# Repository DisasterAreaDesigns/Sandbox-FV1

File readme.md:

# FV-1 Sandbox
FV-1 Sandbox is a self-contained open-source development platform for the Spin FV-1 digital signal processing (DSP) integrated circuit.  

## Background:
The Spin Semiconductor FV-1 IC was developed by Alesis alumni Keith Barr and Frank Thomson.  It features an integrated architecture with built-in analog-to-digital and digital-to-analog converters, memory, and processing core.  It requires only a few external components to operate, and can run user programs from an inexpensive serial EEPROM.  It has been used in hundreds of different pedals and devices, with many hundreds of thousands of units in service.

## Why Are We Doing This?
The FV-1 has seven built-in programs that cover a wide range of effects, but most designers leverage the custom code capabilities of the chip.  The Fv-1 is programmed in SpinASM, a proprietary assembly language.  Spin provided a free integrated development environment for Windows computers called SpinASM IDE.  This interfaces with a development board fitted with a Cypress PSoC microcontroller functioning as a USB interface.  The IDE allows for code editing, rapid auditioning of DSP algorithms on the development board, and production programming using multi-algorithm .SPJ Spin Project files.  No MacOS or Linux programming tools were made available, and SpinASM also had issues running on newer versions of Windows.  A patch was released to fix compatibility issues under Windows 7, and this version (1.1.31) works with most Windows 10 and Windows 11 systems.  The IDE does also run under Windows for ARM, but support for the PSoC-based development board is broken due to driver issues.

Our intention is to create a complete toolchain that can run on any modern computer that interfaces with a high-quality hardware platform for deploying algorithms.  To this end, we have created an open-source assembler that runs in a web browser and a hardware platform that interfaces with an inexpensive RP2040 microcontroller for programming.  The hardware platform may be assembled without the microcontroller for higher-quantity production use, and the RP2040 programmer may be used in conjunction with either a TagConnect programming cable or pin sockets on the PCB for production programming.

## What Did We Do?
We've been using [asfv1](https://github.com/ndf-zz/asfv1), an open-source assembler for FV-1 designed by Nathan Fraser.  It works great but requires a few steps to deploy as part of a larger toolchain.  It works with Sublime Text or Notepad++ to create a DIY development environment, but it's still a lot of work for a new user.  So we decided to build a one-stop shop!

We patched up some bugs we found, added some quality-of-life improvements, and ported the whole thing from Python to JavaScript so we could run it in a browser.  There's a pretty decent code editor using Monaco, an assembler, and a one-button deployment to the Sandbox hardware.

The hardware is very simple, incorporating a high-quality analog front-end that reduces out-of-band and clock noise from the FV-1.  It's full stereo, features three user potentiometer controls, and two toggle switches for selecting one of six possible algorithms.  It also uses program zero to bypass the effect, allowing stereo switching without any external hardware or relays, albeit at the cost of higher noise floor and a slight delay from the DSP ADC+DAC conversions.

Programming is accomplished using the aforementioned RP2040 board - we've used a Waveshare RP2040 Zero for its compact form factor and handy USB-C port, but clones of this part or other variations may also work.  the RP2040 code is implemented in CircuitPython for ease of deployment and modification.  To program a new algorithm on the Sandbox EEPROM, simply copy an assembled .HEX or .BIN file to the RP2040 CIRCUITPY or SANDBOX removable drive.  Name the program 0.HEX to program algorithm zero, 1.HEX for program 1, and so on.  Adding any other named .BIN or .HEX file will write program #3, which is the program accessed if no toggle switches are assembled to the Sandbox PCBA.

We've also added an FV-1 simulator to the web app.  The assembled program runs through a software model of the chip at its native 32.768 kHz, so you can audition an algorithm on a test tone, an audio file, or live input before you ever program the hardware.  The three pot controls are on screen, and each successful build reloads into the simulator while it plays.  Two indicator lamps follow `REG30` and `REG31`.  The simulator models accumulator saturation and the FV-1's companded delay memory, and its LFO rates and depths follow the equations in Spin's application note AN-0001.  Chorus interpolation is approximated, so always confirm a design on real hardware.

The simulator can also be played from a MIDI controller plugged into your computer.  Press **Enable MIDI** in the simulator panel, allow the browser's MIDI prompt, and pick an input and channel.  `CC50`, `CC51` and `CC52` sweep POT0, POT1 and POT2, and `CC102` switches the effect, with `0-63` bypassed and `64-127` engaged.  MIDI moves the same controls the sliders do, at the full 128 steps a control change carries, so a program cannot tell the difference between a fader and a mouse.  Note that the Sandbox pedal itself has no MIDI input - this drives the simulator only.

The simulator can be watched as well as heard.  **Open register viewer**, under **Debug Tools** in the simulator panel, opens a second window (floating above the editor where the browser allows it, with an **Always on top** switch in its header) showing `ACC`, the audio in and out, the pots, the LFOs and `REG0`-`REG31` as the program runs, each as its S.23 value and the 24-bit word behind it, and named after the `EQU` lines in your source.  Click a register there to plot it over time - an audio-rate signal shows as its envelope and an LFO as its shape.  **ACC trace in editor** writes the accumulator after every instruction at the end of its line, live: a `SKP` says whether it was taken, the lines it jumped over say so, and a line whose result had to be clamped shows how often that happens.  The FV-1 runs every instruction every sample, so one pass is a complete trace and there is nothing to step through to see it.

When there is, the **Debug** section halts the simulator and steps it.  **Halt** freezes the core at the end of the current sample; **Step** runs one instruction, **Sample** runs the rest of the pass, and **Run to line** goes on until that line is next, with the editor following, the trace showing this pass up to the halt, and the register viewer updating on every step.  Breakpoints are conditions rather than places, since a bare line would trip on the first sample: click the margin left of a line number for a line breakpoint and give it a first run or a sample number, or halt on a clip, a `SKP` going one way, or `ACC` or a register crossing a value.  While halted the output is silent and the input is held at the halted sample; **Resume** carries on from wherever the stepping got to.

So it's a web app and a pedal.  Hook 'em up and write some code!

## Running the Assembler Locally
The web app needs to be served over http - opening `Assembler/index.html` directly as a `file://` page will not work.  Browsers block the audio engine the simulator depends on from `file://` origins, and the directory and serial access used to talk to the hardware need a secure context too.  `localhost` counts as secure, so any static file server will do:

```
python3 -m http.server 8000 --directory Assembler
```

Then open <http://localhost:8000> in Chrome or Edge.  If you prefer Node, `npx serve Assembler` works the same way.

Chrome or Edge are required for programming hardware and selecting folders, since Firefox and Safari do not implement the File System Access and Web Serial APIs.  The simulator itself works in any browser with AudioWorklet support, and its MIDI control works in Chrome, Edge and Firefox - Safari has no Web MIDI.

## What's In This Repo?
* **ASFV1 Source:**  copies of the Python source for asfv1, the reference assembler this one is checked against
* **Assembler:**  JavaScript Web Application for assembling FV-1 programs, including an in-browser FV-1 simulator (`fv1-emu.js` / `fv1-sim.js`) with MIDI control (`fv1-midi.js`), a register viewer (`fv1-regs.js`), an ACC trace in the editor (`fv1-trace.js`) and a halt-and-step debugger with conditional breakpoints (`fv1-debug.js`)
* **Firmware**  CircuitPython code for the RP2040 Zero program module
* **spin-test**  Puppeteer scripts and sample FV-1 programs for testing the assembler: `npm run test:roundtrip` for the assembler and simulator as a pair, `npm run test:emu` for the DSP core, `npm run test:midi` for the simulator's MIDI control, and `npm run test:page` for the editor's unsaved-changes guard
* **Hardware**  Schematic and PCB files for Sandbox pedal hardware

## What Can I Do With All This?
We've released this project and all associated tools under the [MIT License.](https://www.tldrlegal.com/license/mit-license)  This means that you can use the tools and information in this repository for anything you want, as long as you inform your users / customers / clients that you got it from us.  You can modify or change anything here to suit your purposes, and you can make products that you sell for profit.  You can even close your sources, so that what's in your product or project is private.  You just have to credit us as shown in our [license file.](https://github.com/DisasterAreaDesigns/Sandbox-FV1/blob/main/LICENSE)  An example of what that looks like can be found in our [Third Party Notices](https://github.com/DisasterAreaDesigns/Sandbox-FV1/blob/main/ThirdPartyNotices.txt) file.

Any projects you create with these tools belong to you.  If you write your own code to process audio with this project, that code is under your copyright and is yours to do with what you wish.  If you use someone else's DSP algorithms, that use will be subject to *their* license terms, and we're not able to help you sort that out.  TL:DR you can do whatever you want with this repo, just give us credit.

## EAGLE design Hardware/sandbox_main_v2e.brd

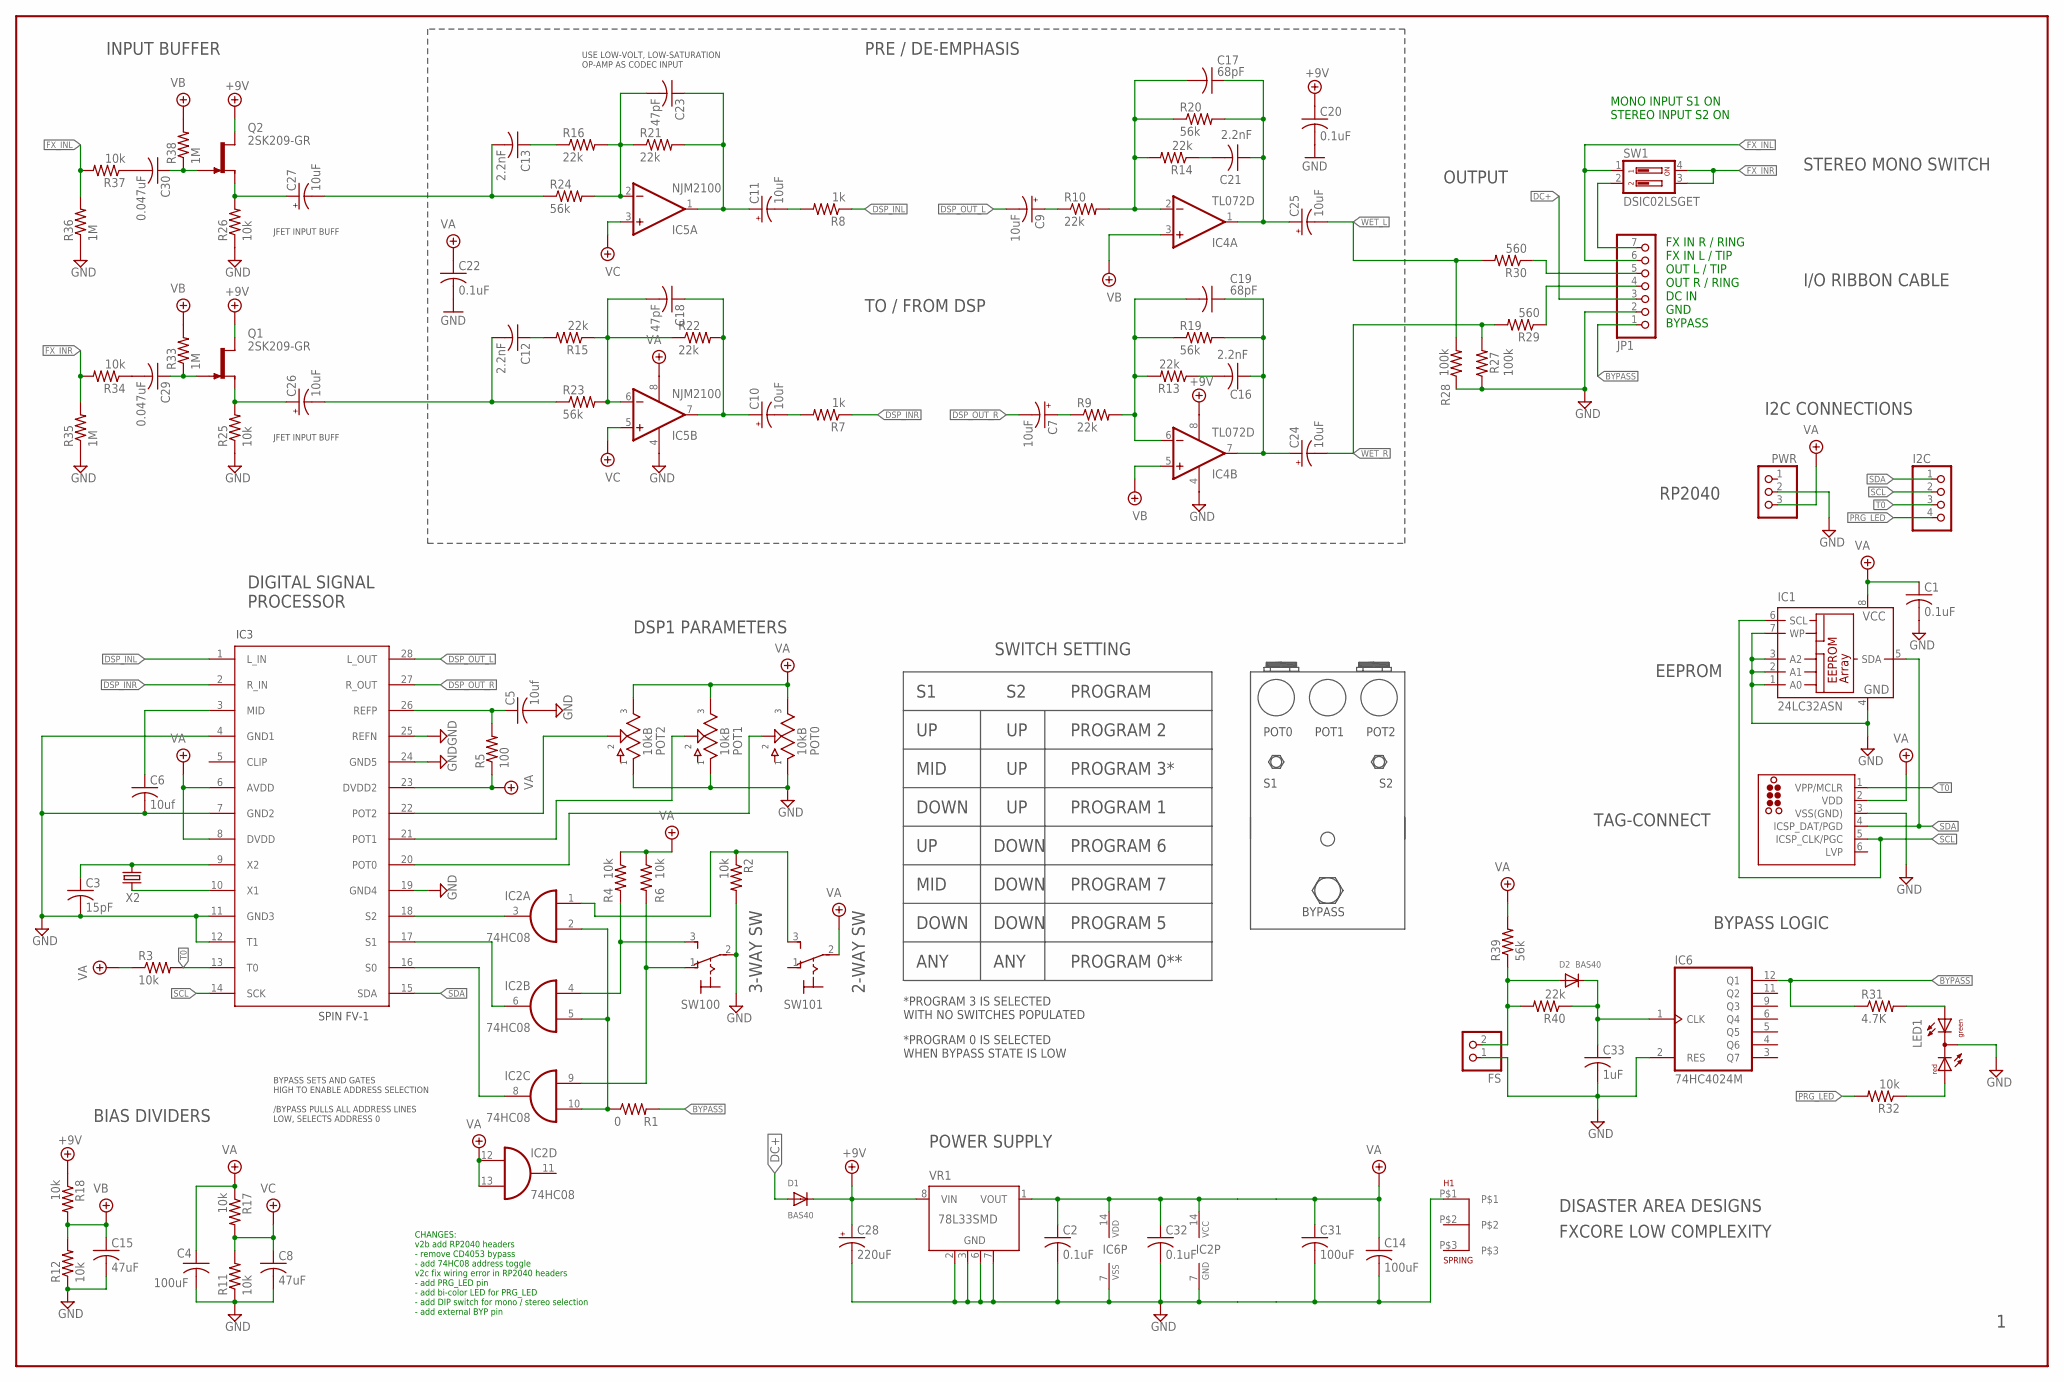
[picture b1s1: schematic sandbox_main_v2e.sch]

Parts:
C1, C2, C20, C22, C32: 0.1uF; C0805K
C3: 15pF; C0805K
C4, C14, C31: 100uF; C1206K
C5, C6: 10uf; C0805K
C7, C9, C10, C11, C24, C25, C26, C27: 10uF; CT3216
C8, C15: 47uF; C1206K
C12, C13, C16, C21: 2.2nF; C0805K
C17, C19: 68pF; C0805K
C18, C23: 47pF; C0805K
C28: 220uF; PANASONIC_D
C29, C30: 0.047uF; C1206K
C33: 1uF; C0805K
D1, D2: BAS40; SOT23-R
FS: PINHD-1X2; 1X02
H1: 628
I2C: PINHD-1X4; 1X04
IC1: 24LC32ASN; SO-08
IC2: 74HC08; SO14
IC3: SPINFV-1; SOIC-28
IC4: TL072D; SO08
IC5: NJM2100; SO08
IC6: 74HC4024M; SO14
JP1: PINHD-1X7; 1X07
LED1: DUOLED-RG-C; DUOLED-C-5MM
POT0, POT1, POT2: 10kB; POT_9MM_PACK_SM
PWR: PINHD-1X3; 1X03
Q1, Q2: 2SK209-GR; SOT-23
R1: 0; R0805
R2, R3, R4, R6, R11, R12, R17, R18, R25, R26, R32, R34, R37: 10k; R0805
R5: 100; R0805
R7, R8: 1k; R0805
R9, R10, R13, R14, R15, R16, R21, R22, R40: 22k; R0805
R19, R20, R23, R24, R39: 56k; R0805
R27, R28: 100k; R0805
R29, R30: 560; R0805
R31: 4.7K; R0805
R33, R35, R36, R38: 1M; R0805
SW1: DSIC02LSGET; CTS-219-02
SW100, SW101: 320-916
TC1: TC2030_ICSP-MCP-NL; TC2030-MCP-NL
VR1: 78L33SMD; SO08
X2: 32.768kHz; CRYSTAL-SMD-3.2X1.5MM

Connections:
+9V: C20.1, C28.+, D1.3 (C), IC4.8 (V+), Q1.2 (D), Q2.2 (D), R18.1, VR1.8 (VIN)
BYPASS: IC6.12 (Q1), JP1.1, R1.2, R31.1
BYPASS_IC: IC2.2 (I1), IC2.5 (I1), IC2.10 (I1), R1.1
DC+: D1.1 (A), JP1.3
DSP_INL: IC3.1 (L_IN), R8.1
DSP_INR: IC3.2 (R_IN), R7.1
DSP_OUT_L: C9.-, IC3.28 (L_OUT)
DSP_OUT_R: C7.-, IC3.27 (R_OUT)
FX_INL: JP1.6, R36.2, R37.2, SW1.1
FX_INR: R34.2, R35.2, SW1.3, SW1.4
GND: C1.2, C2.2, C3.2, C4.2, C5.2, C6.2, C8.2, C14.2, C15.2, C20.2, C22.2, C28.-, C31.2, C32.2, C33.2, FS.1, H1.P$1, IC1.1 (A0), IC1.2 (A1), IC1.3 (A2), IC1.4 (GND), IC1.7 (WP), IC2.7 (GND), IC3.4 (GND1), IC3.7 (GND2), IC3.11 (GND3), IC3.12 (T1), IC3.19 (GND4), IC3.24 (GND5), IC3.25 (REFN), IC4.4 (V-), IC5.4 (V-), IC6.2 (RES), IC6.7 (VSS), JP1.2, LED1.C, POT0.P$1, POT1.P$1, POT2.P$1, PWR.2, R2.2, R11.1, R12.1, R25.1, R26.1, R27.1, R28.1, R35.1, R36.1, SW100.2, TC1.3 (VSS(GND)), VR1.2 (GND), VR1.3 (GND), VR1.6 (GND), VR1.7 (GND)
unnamed: IC3.10 (X1), X2.P$1 (1)
unnamed: IC2.3 (O), IC3.18 (S2)
unnamed: C29.1, Q1.3 (G), R33.1
unnamed: IC2.6 (O), IC3.17 (S1)
unnamed: C29.2, R34.1
unnamed: IC2.8 (O), IC3.16 (S0)
unnamed: C11.+, C23.1, IC5.1 (OUT), R21.2
unnamed: C23.2, IC5.2 (-IN), R16.2, R21.1, R24.2
unnamed: C12.2, C26.-, R23.1
unnamed: C12.1, R15.2
unnamed: LED1.AR, R32.1
unnamed: JP1.7, SW1.2
unnamed: C13.1, R16.1
unnamed: C5.1, IC3.26 (REFP), R5.2
unnamed: C13.2, C27.-, R24.1
unnamed: C10.-, R7.2
unnamed: C6.1, IC3.3 (MID)
unnamed: C18.2, IC5.6 (-IN), R15.1, R22.1, R23.2
unnamed: C10.+, C18.1, IC5.7 (OUT), R22.2
unnamed: C17.2, IC4.2 (-IN), R10.2, R14.2, R20.1
unnamed: C11.-, R8.2
unnamed: C19.2, IC4.6 (-IN), R9.2, R13.2, R19.1
unnamed: C30.2, R37.1
unnamed: C7.+, R9.1
unnamed: C16.2, R13.1
unnamed: C16.1, C19.1, C24.+, IC4.7 (OUT), R19.2
unnamed: C9.+, R10.1
unnamed: JP1.5, R30.1
unnamed: C21.2, R14.1
unnamed: C17.1, C21.1, C25.+, IC4.1 (OUT), R20.2
unnamed: JP1.4, R29.1
unnamed: C33.1, D2.3 (C), IC6.1 (CLK), R40.1
unnamed: D2.1 (A), FS.2, R39.1, R40.2
unnamed: LED1.AX (AG), R31.2
unnamed: C3.1, IC3.9 (X2), X2.P$2 (2)
unnamed: C26.+, Q1.1 (S), R25.2
unnamed: C27.+, Q2.1 (S), R26.2
unnamed: C30.1, Q2.3 (G), R38.1
P0: IC3.20 (POT0), POT0.P$2
P1: IC3.21 (POT1), POT1.P$2
P2: IC3.22 (POT2), POT2.P$2
PRG_LED: I2C.4, R32.2
S0: IC2.9 (I0), R6.2, SW100.1 (O)
S1: IC2.4 (I0), R4.2, SW100.3 (S)
S2: IC2.1 (I0), R2.1, SW101.3 (S)
SCL: I2C.2, IC1.6 (SCL), IC3.14 (SCK), TC1.5 (ICSP_CLK/PGC)
SDA: I2C.1, IC1.5 (SDA), IC3.15 (SDA), TC1.4 (ICSP_DAT/PGD)
T0: I2C.3, IC3.13 (T0), R3.2, TC1.1 (VPP/MCLR)
VA: C1.1, C2.1, C4.1, C14.1, C22.1, C31.1, C32.1, IC1.8 (VCC), IC2.12 (I0), IC2.13 (I1), IC2.14 (VCC), IC3.6 (AVDD), IC3.8 (DVDD), IC3.23 (DVDD2), IC5.8 (V+), IC6.14 (VDD), POT0.P$3, POT1.P$3, POT2.P$3, PWR.3, R3.1, R4.1, R5.1, R6.1, R17.1, R39.2, SW101.2, TC1.2 (VDD), VR1.1 (VOUT)
VB: C15.1, IC4.3 (+IN), IC4.5 (+IN), R12.2, R18.2, R33.2, R38.2
VC: C8.1, IC5.3 (+IN), IC5.5 (+IN), R11.2, R17.2
WET_L: C25.-, R28.2, R30.2
WET_R: C24.-, R27.2, R29.2

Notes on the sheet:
POWER SUPPLY
DIGITAL SIGNAL PROCESSOR
INPUT BUFFER
FXCORE LOW COMPLEXITY
DSP1 PARAMETERS
3-WAY SW
DISASTER AREA DESIGNS
OUTPUT
POT2
POT1
POT0
BYPASS
BIAS DIVIDERS
SWITCH SETTING
MID
DOWN
PROGRAM 3*
PROGRAM 2
PROGRAM 1
PRE / DE-EMPHASIS
BYPASS LOGIC
USE LOW-VOLT, LOW-SATURATION OP-AMP AS CODEC INPUT
JFET INPUT BUFF
FX IN R / RING FX IN L / TIP OUT L / TIP OUT R / RING DC IN GND BYPASS
PROGRAM 7
PROGRAM 6
PROGRAM 5
PROGRAM
*PROGRAM 3 IS SELECTED WITH NO SWITCHES POPULATED
2-WAY SW
I2C CONNECTIONS
BYPASS SETS AND GATES HIGH TO ENABLE ADDRESS SELECTION /BYPASS PULLS ALL ADDRESS LINES LOW, SELECTS ADDRESS 0
CHANGES: v2b add RP2040 headers - remove CD4053 bypass - add 74HC08 address toggle v2c fix wiring error in RP2040 headers - add PRG_LED pin - add bi-color LED for PRG_LED - add DIP switch for mono / stereo selection - add external BYP pin
ANY
PROGRAM 0**
*PROGRAM 0 IS SELECTED WHEN BYPASS STATE IS LOW
MONO INPUT S1 ON STEREO INPUT S2 ON
SPIN FV-1
IC3
I/O RIBBON CABLE

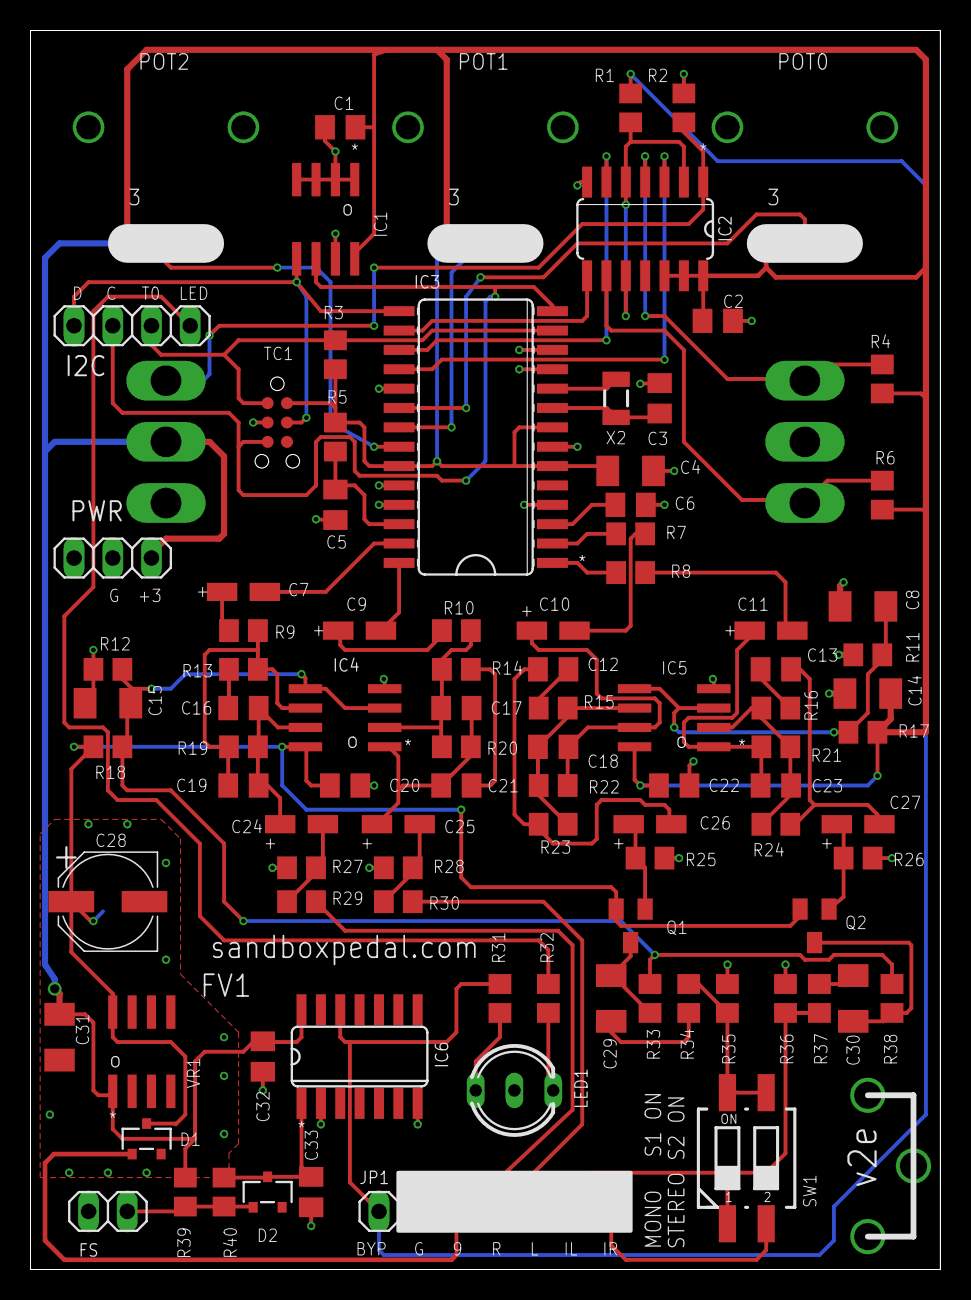
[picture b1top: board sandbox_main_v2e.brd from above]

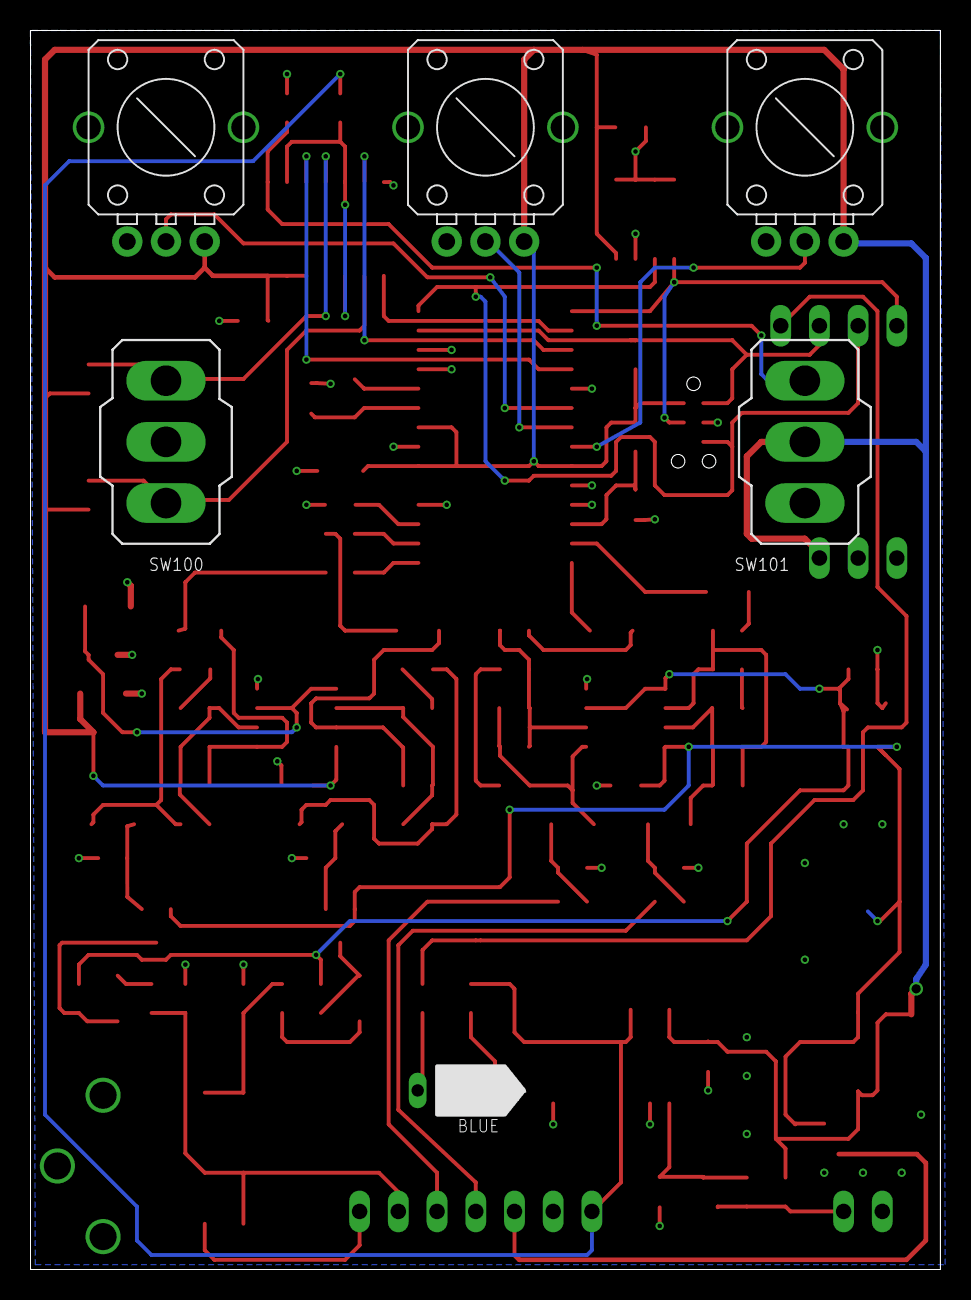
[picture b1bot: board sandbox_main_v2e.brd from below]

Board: 2 copper layers, 59.7 x 81.3 mm, 98 parts (2 on the bottom side), 64 nets.

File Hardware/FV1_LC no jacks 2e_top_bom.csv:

Comment,Designator,Footprint,LCSC Part #,Type
0,R1,R0805,,SMD
0.1uF,C1 C2 C20 C22 C32,C0805K,,SMD
0.047uF,C29 C30,C1206K,,SMD
1M,R33 R35 R36 R38,R0805,,SMD
1k,R7 R8,R0805,,SMD
1uF,C33,C0805K,,SMD
2.2nF,C12 C13 C16 C21,C0805K,,SMD
2SK209-GR,Q1 Q2,SOT-23,,SMD
4.7K,R31,R0805,,SMD
10k,R2 R3 R4 R6 R11 R12 R17 R18 R25 R26 R32 R34 R37,R0805,,SMD
10kB,POT0 POT1 POT2,POT_9MM_PACK_SM,,THT
10uF,C7 C9 C10 C11 C24 C25 C26 C27,CT3216,,SMD
10uf,C5 C6,C0805K,,SMD
15pF,C3,C0805K,,SMD
22k,R9 R10 R13 R14 R15 R16 R21 R22 R40,R0805,,SMD
24LC32ASN,IC1,SO-08,,SMD
32.768kHz,X2,CRYSTAL-SMD-3.2X1.5MM,,SMD
47pF,C18 C23,C0805K,,SMD
47uF,C8 C15,C1206K,,SMD
56k,R19 R20 R23 R24 R39,R0805,,SMD
68pF,C17 C19,C0805K,,SMD
74HC08,IC2,SO14,,SMD
74HC4024M,IC6,SO14,,SMD
78L33SMD,VR1,SO08,,SMD
100,R5,R0805,,SMD
100k,R27 R28,R0805,,SMD
100uF,C4 C14 C31,C1206K,,SMD
220uF,C28,PANASONIC_D,,SMD
560,R29 R30,R0805,,SMD
628,H1,628,,THT
BAS40,D1 D2,SOT23-R,,SMD
DSIC02LSGET,SW1,CTS-219-02,,SMD
NJM2100,IC5,SO08,,SMD
SPINFV-1,IC3,SOIC-28,,SMD
TL072D,IC4,SO08,,SMD

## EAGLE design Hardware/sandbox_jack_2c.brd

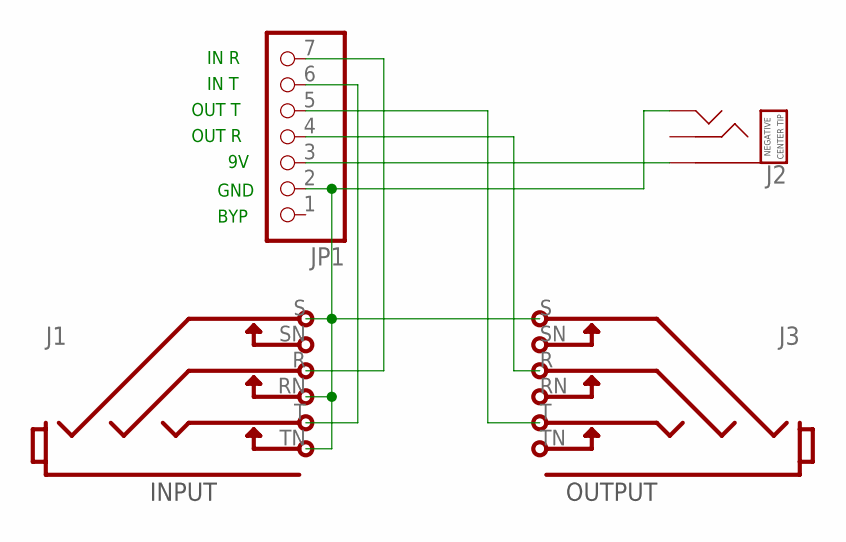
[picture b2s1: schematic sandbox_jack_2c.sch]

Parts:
J1, J3: STEREOSW3NOMOUNT; NEUTRIK-NRJ6HF-NOMOUNT
J2: DC_TRS; JACK_DC_PC-MOUNT_2.1MM_NO-KEEPOUT
JP1: PINHD-1X7; 1X07

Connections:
JACK_GND: J1.RN, J1.S, J1.TN, J2.3 (GND), J3.S, JP1.2
unnamed: J1.R, JP1.7
unnamed: J2.1 (PWR), JP1.3
unnamed: J1.T, JP1.6
unnamed: J3.T, JP1.5
unnamed: J3.R, JP1.4

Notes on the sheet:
INPUT
OUTPUT
GND
OUT T
IN T
OUT R
IN R
BYP

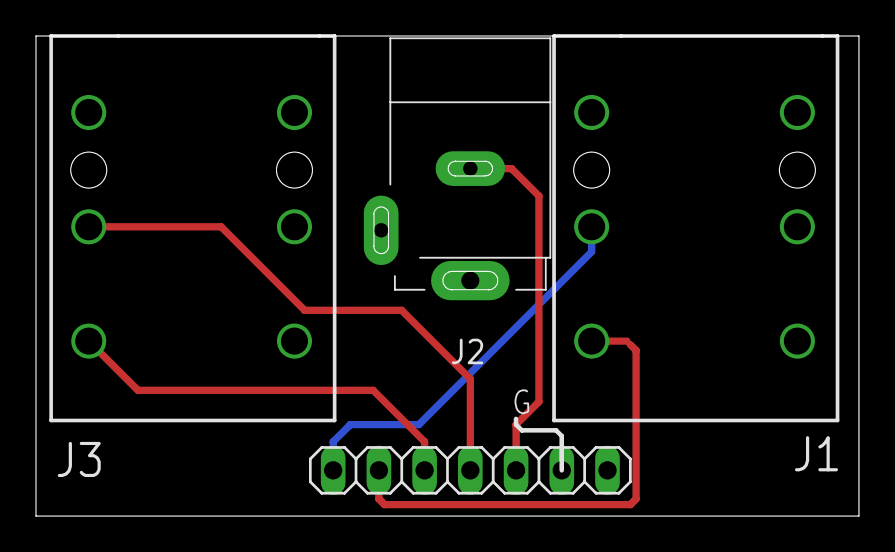
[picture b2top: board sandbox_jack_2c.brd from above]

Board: 2 copper layers, 45.7 x 26.7 mm, 4 parts (0 on the bottom side), 6 nets.

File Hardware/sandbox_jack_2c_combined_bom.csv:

Comment,Designator,Footprint,LCSC Part #,Type
,JP1,1X05,,THT
DC_TRS,J2,JACK_DC_PC-MOUNT_2.1MM_NO-KEEPOUT,,THT
STEREOSW3NOMOUNT,J1 J3,NEUTRIK-NRJ6HF-NOMOUNT,,THT

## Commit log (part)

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2025-08-01 Added readme.md
2025-08-01 Added readmes
2025-08-04 Initial commit
    Changed plaintext editor to use monaco instead
2025-08-04 Updated editor version
    Added icon, search / find text, title
2025-08-04 Fix issue with saving source
2025-08-04 Added favico
2025-08-04 Clean up, change examples to grid
2025-08-04 removed test file
2025-08-04 Update Program Selection grid
2025-08-04 Update readme.md
    Spelling and grammar
2025-08-05 Scroll window to top on load
2025-08-06 Update readme
    Added license terms and info
2025-08-06 Add .gitignore
2025-08-06 Build 10
    Split assembler and examples into their own files
    added modal popups to prevent accidental clearing
    added note to editor window re: ascii only
2025-08-06 Added proper dark mode
2025-08-06 Update gitignore
2025-08-06 Updated license info
2025-08-06 Build 11
    Refactor to move monaco to its own file
2025-08-07 Update editor shortcut text
2025-08-07 Build 12
    Added instructionf flyout
    Added schematic for v2c board
2025-08-07 Added checks for hardware_id.json on RP2040 target
    Added firmware binary for RP2040 target
    Added hardware_id.json file
2025-08-08 UI changes
    Select 3.hex as default
    Clear assembly output window on editor clear or example load
2025-08-09 Build 13
    Added Download C Header button
    fixed issue with resolving skip targets
    fixed issue with S1_14 encoding
    fixed issue with register resolution
2025-08-10 Build 14
    Fixed issues with numeric parser using math.round(), replaced with math.floor() to match SpinASM behaviour
2025-08-12 Remove .DS_Store files and add to .gitignore
2025-08-12 Add drag and drop to monaco editor
2025-08-13 Build 15
    Added readonly text to editor
    Replaced hardcoded debug statements with debuglog()
    added debuglog.js to handle debuglog() reporting
    added full build results checkbox
    changed results window to scroll
    added spinasm build reporting like fxcore version
2025-08-13 Refactor RP2040 firmware
    Added complete fw blob UF2
    removed adafruit UF2 blob
    updated BOOT.PY for USB VID/PID info (preliminary, will change)
2025-08-13 Build 16
    Added clear hardware button
    Added serial connect button
    Added serial connect functions to ui.js
    Updated RP2040 code.py to ignore zero-byte hex files, prevents undesired updates at boot
    unified and cleaned CSS
2025-08-13 Add "all" program to RP2040 for SpinCAD compatibility
    Add "all.hex" as option for RP2040, this will program all eeprom bytes from single file
    Added file size checks to RP2040 program, ensures we don't program the whole eeprom from a random hex file
    Add "all" as target for clear hardware
    make monaco not-draggable
2025-08-16 Added fonts
2025-08-16 Added fontsBuild 16
    debug_config.js: fixed issue with logging all data to console
    index.html: ui cleanup, match FXCore version
    - add user-preferences options
    - add set project folder button
    styles.css: added styling for project button
    ui.js: added project button handling
2025-08-16 UI changes
    index.html: updated save and load functions, added project folder selection with better selector
    monaco.js added change detection stuff from fxcore
    styles.css removed custom styling for project folder select, no longer needed
    ui.js resolved issue with download picker
    - fixed download functions, now will land in same directory with correct filename
    - rework all load functions to fire modal and update teh hascontentchanged stuff
2025-08-16 minor cleanup
    remove icon, using SVGs now
    change CSS to light up selectors in light mode, whoops
    removed redundant DOMLoaded section
    added updatehardwareconnectionstatus() function to make this tidier, like FXCore
2025-08-21 Build 17
    Incorporated flyout options + info
    Added instruction set reference
    Added keyboard shortcuts to match FXCore
    Fixed editor stealing shortcuts for assemble / download / clear
2025-08-21 Fix download button
    Needed to call updatedownloabuttonstatus() when selecting output directory
    fixed page title as set by Monaco (FV-1 Assembler *)
    removed references to FXCore
2025-08-21 Added EEPROM dump function
    Removed [SERIAL] tags from messages
    Increased message history length
2025-08-21 Clean up spacing and unwanted text
    Added code.py for dumping eeprom. send dumpEEPROM() in console
2025-09-24 Updated for v2e hardware (stereo + LED on GP3)
    Added second LED controls
2025-09-29 Added file name display to editor
2025-10-03 Add files via upload
    Bill of materials for hardware rev 2e PCBA
2025-10-03 Add files via upload
    Schematic File
2025-10-03 Update boot.py to reflect new USB VID:PID
2025-10-05 Testing control pin changes
    Attempting to prevent weird noises during programming
2025-10-07 Added gerbers and EAGLE files to Hardware folder
2025-10-07 Rename sandbox_main_v2e_schematic.pdf to sandbox_full_v2e_schematic.pdf
    Renamed fle
2025-10-25 Add documentation
2026-04-09 Added production programmer firmware
2026-04-09 Update production prog to work with named HEX files
    Also added TEST mode (change line 92)
2026-06-14 Rename Firmware/production programmer/code-test.py to Firmware/production programmer/archive/code-test.py
2026-06-14 Rename Firmware/production programmer/code-working.py to Firmware/production programmer/archive/code-working.py

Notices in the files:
parts and their libraries:
tag-connect: ©2009 ROFA.cz - modified and updated by Robert Darlington ‹rdarlington@gmail.com›
